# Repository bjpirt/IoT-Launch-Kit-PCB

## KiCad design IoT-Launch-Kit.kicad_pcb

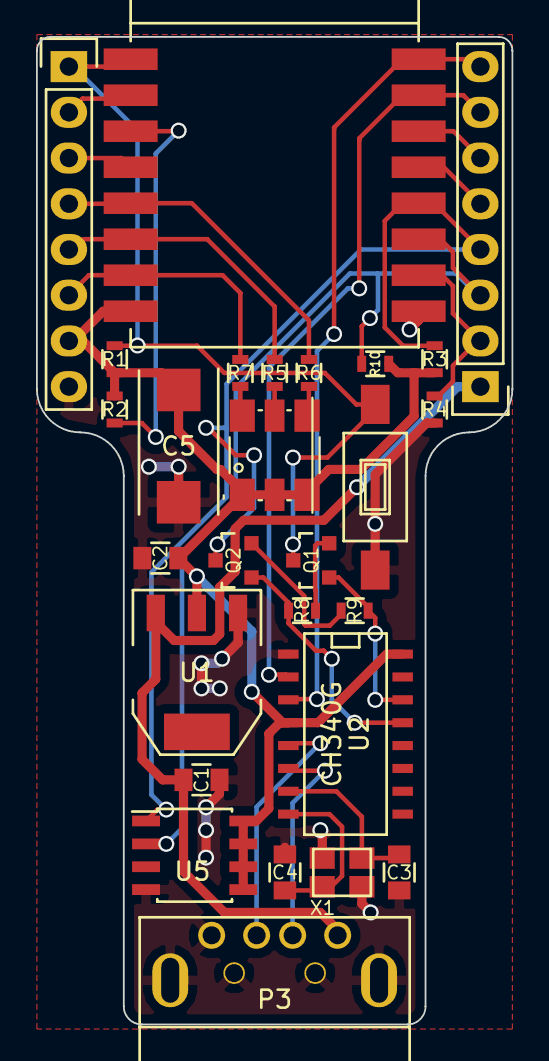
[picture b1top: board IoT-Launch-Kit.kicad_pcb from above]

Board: 2 copper layers, 26.4 x 54.9 mm, 28 parts (1 on the bottom side), 28 nets.

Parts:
C1, C2: 10uF; C_0805
C3, C4: 22pF; C_0805
C5: 100uF; TantalC_SizeD_EIA-7343_Reflow
D1: LED_RGB; LED-RGB-5050
P1, P2: CONN_01X08; Pin_Header_Straight_1x08
P3: USB_A
Q1, Q2: S8050; SOT-23
R1, R2, R3, R4, R8, R9, R10: 10k; R_0603
R5, R6, R7: 300R; R_0603
SW1: SPST; SW_SPST_FSMSM
SpaceshipLogo: G***; SpaceshipLogo
U1: LD1117S33CTR; SOT-223
U2: CH340G; SO-16-N
U3: ESP-12
U5: LM75A; SOIC-8_3.9x4.9mm_Pitch1.27mm
X1: CRYSTAL_SMD; crystal_FA238-TSX3225

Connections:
+3V3: C2.1, C5.1, D1.BA, D1.GA, D1.RA, P1.7, R1.2, R2.2, R3.2, R10.2, U1.2, U2.4, U2.16, U3.8, U5.5, U5.6, U5.7, U5.8
+5V: C1.1, P2.1, P3.1, U1.3
ADC: P1.2, U3.2
DIN: P2.7, U2.2, U3.15
DOUT: P2.8, U2.3, U3.16
DTR: Q2.1, R8.1, U2.13
GND: C1.2, C2.2, C3.2, C4.2, C5.2, P1.8, P3.4, P3.5, R4.1, SW1.1, U1.1, U2.1, U3.9, U5.4, X1.3
GPIO0: P2.4, Q2.3, R3.1, U3.12, U5.1
GPIO2: P2.3, R10.1, U3.11, U5.2
GPIO4: P2.5, U3.13
GPIO5: P2.6, U3.14
GPIO12: P1.5, R5.2, U3.6
GPIO13: P1.6, R7.2, U3.7
GPIO14: P1.4, R6.2, U3.5
GPIO15: P2.2, R4.2, U3.10
GPIO16: P1.3, U3.4
unnamed: C3.1, U2.7, X1.1
unnamed: C4.1, U2.8, X1.2
unnamed: D1.BC, R7.1
unnamed: D1.GC, R6.1
unnamed: D1.RC, R5.1
unnamed: P3.2, U2.6
unnamed: P3.3, U2.5
unnamed: Q1.2, R8.2
unnamed: Q2.2, R9.2
unnamed: R2.1, U3.3
RST: P1.1, Q1.3, R1.1, SW1.2, U3.1
RTS: Q1.1, R9.1, U2.14

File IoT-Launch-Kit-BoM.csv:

Reference, Value, Footprint, Datasheet
U1,LD1117S33CTR,TO_SOT_Packages_SMD:SOT-223,
C1,10uF,Capacitors_SMD:C_0805,
U2,CH340G,SMD_Packages:SO-16-N,
C4,22pF,Capacitors_SMD:C_0805,
C3,22pF,Capacitors_SMD:C_0805,
U3,ESP-12,IoT-Launch-Kit:ESP-12,
C5,100uF,Capacitors_Tantalum_SMD:TantalC_SizeD_EIA-7343_Reflow,
R2,10k,Resistors_SMD:R_0603,
R1,10k,Resistors_SMD:R_0603,
R3,10k,Resistors_SMD:R_0603,
R4,10k,Resistors_SMD:R_0603,
D1,LED_RGB,IoT-Launch-Kit:LED-RGB-5050,
R5,300R,Resistors_SMD:R_0603,
R6,300R,Resistors_SMD:R_0603,
R7,300R,Resistors_SMD:R_0603,
U5,LM75A,Housings_SOIC:SOIC-8_3.9x4.9mm_Pitch1.27mm,
SW1,SPST,Buttons_Switches_SMD:SW_SPST_FSMSM,
Q2,S8050,TO_SOT_Packages_SMD:SOT-23,
Q1,S8050,TO_SOT_Packages_SMD:SOT-23,
R8,10k,Resistors_SMD:R_0603,
R9,10k,Resistors_SMD:R_0603,
X1,CRYSTAL_SMD,Crystals:crystal_FA238-TSX3225,
C2,10uF,Capacitors_SMD:C_0805,
P3,USB_A,IoT-Launch-Kit:USB_A,
P1,CONN_01X08,Pin_Headers:Pin_Header_Straight_1x08,
P2,CONN_01X08,Pin_Headers:Pin_Header_Straight_1x08,
R10,10k,Resistors_SMD:R_0603,

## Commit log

2015-11-26 Add gitignore file
2015-11-26 Initial commit of the IoT Launch Kit
2015-11-26 Fix path references
2016-01-06 v0.2 of the IoT Launch Kit: - onboard temperature sensor - only use the side pins of the ESP12 module - rearrange pin usage - slim form factor for fitting into USB slot - NodeMCU style reset circuit

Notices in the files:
IoT-Launch-Kit.kicad_pcb:
© 2016 Ben Pirt
